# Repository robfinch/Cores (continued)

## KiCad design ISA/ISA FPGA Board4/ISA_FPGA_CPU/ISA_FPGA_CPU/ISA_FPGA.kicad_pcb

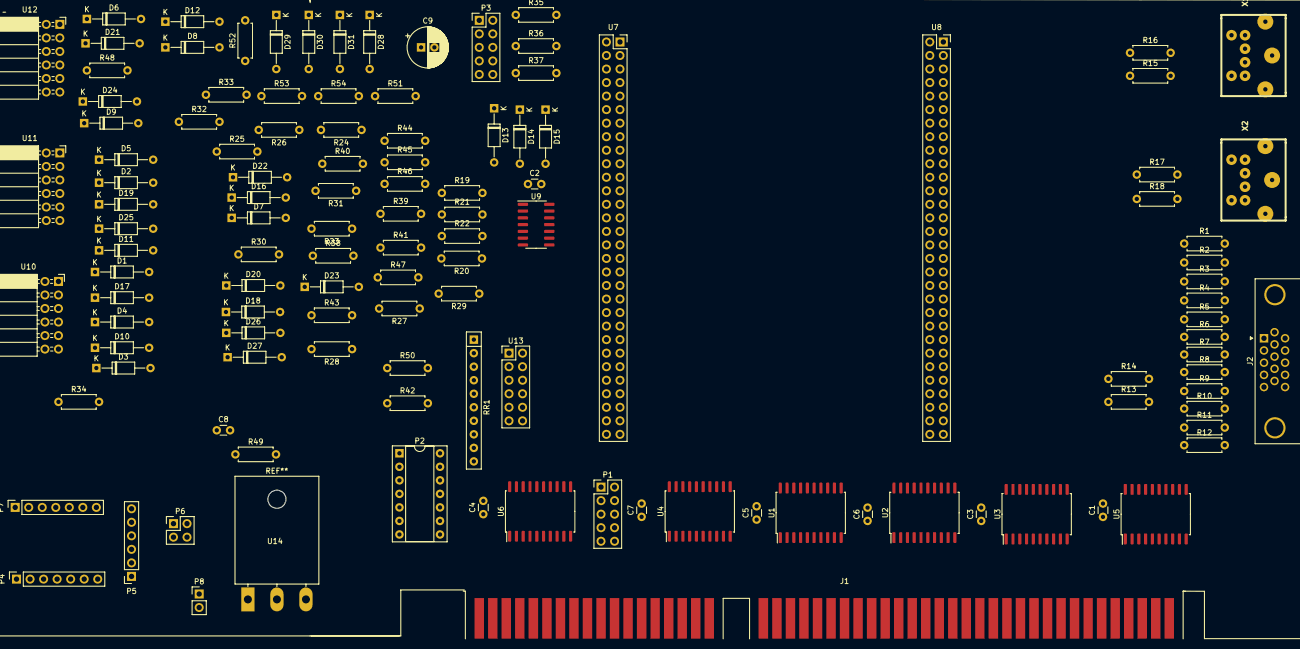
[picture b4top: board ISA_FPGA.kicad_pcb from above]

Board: 2 copper layers, 121 parts (0 on the bottom side), 207 nets, no tracks yet.

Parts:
C1, C2, C3, C4, C5, C6, C7, C8: 0.1; C_Disc_D3.0mm_W1.6mm_P2.50mm
C9: 10uF; CP_Radial_D7.5mm_P2.50mm
D1, D2, D3, D4, D5, D6, D7, D8, D9, D10, D11, D12, D13, D14, D15, D16, D17, D18, D19, D20, D21, D22, D23, D24, D25, D26, D27: ZPDxx; D_DO-35_SOD27_P10.16mm_Horizontal
D28, D29, D30, D31: LED; D_DO-35_SOD27_P10.16mm_Horizontal
J1: Bus_ISA_16bit; BUS_AT
J2: DE15; DSUB-15-HD_Female_Horizontal_P2.29x1.98mm_EdgePinOffset3.03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
P1, P3: CONN_5X2; PinHeader_2x05_P2.54mm_Vertical
P2: 14.31818MHz; DIP-14_W7.62mm_Socket
P4, P7: CONN_7; PinSocket_1x07_P2.54mm_Vertical
P5: CONN_6; PinSocket_1x06_P2.54mm_Vertical
P6: CONN_2X2; PinHeader_2x02_P2.54mm_Vertical
P8: CONN_2; PinHeader_1x02_P2.54mm_Vertical
R1, R5, R9: 510; R_Axial_DIN0207_L6.3mm_D2.5mm_P7.62mm_Horizontal
R2, R6, R10: 1k; R_Axial_DIN0207_L6.3mm_D2.5mm_P7.62mm_Horizontal
R3, R7, R11: 2k; R_Axial_DIN0207_L6.3mm_D2.5mm_P7.62mm_Horizontal
R4, R8, R12: 4k; R_Axial_DIN0207_L6.3mm_D2.5mm_P7.62mm_Horizontal
R13, R14, R35, R36, R37, R51, R52, R53, R54: 100; R_Axial_DIN0207_L6.3mm_D2.5mm_P7.62mm_Horizontal
R15, R16, R17, R18, R23, R24, R25, R26, R27, R28, R29, R30, R31, R32, R33, R34, R38, R39, R40, R41, R42, R43, R44, R45, R46, R47, R48, R49: 200; R_Axial_DIN0207_L6.3mm_D2.5mm_P7.62mm_Horizontal
R19, R20, R21, R22: 2k2; R_Axial_DIN0207_L6.3mm_D2.5mm_P7.62mm_Horizontal
R50: 10K; R_Axial_DIN0207_L6.3mm_D2.5mm_P7.62mm_Horizontal
RR1: 10k; R_Array_SIP10
U1, U2, U3, U4, U5, U6: 74LVC245; SOIC-20W_7.5x12.8mm_P1.27mm
U7, U8: CONN_30X2; PinSocket_2x30_P2.54mm_Vertical
U9: 74LVC06; SOIC-14_3.9x8.7mm_P1.27mm
U10, U11, U12: CONN_6x2; PinSocket_2x06_P2.54mm_Horizontal
U13: CONN_6x2; PinHeader_2x06_P2.54mm_Vertical
U14: LM3940; LMxx
X1, X2: MINI_DIN_6; PS2

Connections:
/A1: J1.61, U1.3
/A2: J1.60, U1.4
/A3: J1.59, U1.5
/A4: J1.58, U1.6
/A5: J1.57, U1.7
/A6: J1.56, U1.8
/A7: J1.55, U1.9
/A8: J1.54, U2.2
/A9: J1.53, U2.3
/A10: J1.52, U2.4
/A11: J1.51, U2.5
/A12: J1.50, U2.6
/A13: J1.49, U2.7
/A14: J1.48, U2.8
/A15: J1.47, U2.9
/A16: J1.46, U3.2
/A17: J1.45, U3.3
/A18: J1.44, U3.4
/A19: J1.43, U3.5
/A20: J1.88, U3.6
/A21: J1.87, U3.7
/A22: J1.86, U3.8
/A23: J1.85, U3.9
/A24: J1.84, U4.2
/A25: J1.83, U4.3
/A26: J1.82, U4.4
/ALE: J1.28, U4.5
/ANA0: R35.2, U8.11
/ANA1: R36.2, U7.26
/ANA2: R37.2, U7.25
/BLUE0: R4.1, U8.36
/BLUE1: R3.1, U8.34
/BLUE2: R2.1, U8.32
/BLUE3: R1.1, U8.30
/CFG0: RR1.2, U7.48, U13.1
/CFG1: RR1.3, U7.50, U13.3
/CFG2: RR1.4, U7.52, U13.5
/CFG3: RR1.5, U7.54, U13.7
/CFG4: RR1.6, U8.28, U13.9
/D0: J1.40, U5.2
/D1: J1.39, U5.3
/D2: J1.38, U5.4
/D3: J1.37, U5.5
/D4: J1.36, U5.6
/D5: J1.35, U5.7
/D6: J1.34, U5.8
/D7: J1.33, U5.9
/D8: J1.91, U6.9
/D9: J1.92, U6.8
/D10: J1.93, U6.7
/D11: J1.94, U6.6
/D12: J1.95, U6.5
/D13: J1.96, U6.4
/D14: J1.97, U6.3
/D15: J1.98, U6.2
/FA1: U1.17, U8.5
/FA2: U1.16, U8.7
/FA3: U1.15, U8.9
/FA4: U1.14, U8.10
/FA5: U1.13, U8.13
/FA6: U1.12, U8.15
/FA7: U1.11, U8.17
/FA8: U2.18, U8.19
/FA9: U2.17, U8.21
/FA10: U2.16, U8.23
/FA11: U2.15, U8.25
/FA12: U2.14, U8.27
/FA13: U2.13, U8.29
/FA14: U2.12, U8.31
/FA15: U2.11, U8.33
/FA16: U3.18, U8.49
/FA17: U3.17, U8.47
/FA18: U3.16, U8.45
/FA19: U3.15, U8.43
/FA20: U3.14, U8.41
/FA21: U3.13, U8.39
/FA22: U3.12, U8.37
/FA23: U3.11, U8.35
/FA24: U4.18, U8.51
/FA25: U4.17, U8.53
/FA26: U4.16, U8.55
/FALE: U4.15, U8.14
/FD0: U5.18, U7.20
/FD1: U5.17, U7.18
/FD2: U5.16, U7.16
/FD3: U5.15, U7.14
/FD4: U5.14, U7.12
/FD5: U5.13, U7.8
/FD6: U5.12, U7.6
/FD7: U5.11, U7.4
/FD8: U6.11, U7.38
/FD9: U6.12, U7.36
/FD10: U6.13, U7.34
/FD11: U6.14, U7.32
/FD12: U6.15, U7.30
/FD13: U6.16, U7.28
/FD14: U6.17, U7.24
/FD15: U6.18, U7.22
/FDBE*: U5.19, U6.19, U8.20
/FRX: R50.1, U8.26
/FTX: P6.3, U8.24
/FWR: R19.1, U5.1, U6.1, U8.16, U9.2
/GREEN0: R8.1, U8.44
/GREEN1: R7.1, U8.42
/GREEN2: R6.1, U8.40
/GREEN3: R5.1, U8.38
/HS: R13.1, U8.56
/IRQ: U8.22, U9.9
/IRQ*: P1.1, P1.3, P1.5, P1.7, P1.9, R21.1, U9.8
/KBDCLK: R15.1, U8.6
/KBDDAT: R16.1, U8.4
/LED0: R51.1, U7.40
/LED1: R52.1, U7.42
/LED2: R53.1, U7.44
/LED3: R54.1, U7.46
/MSECLK: R18.1, U8.12
/MSEDAT: R17.1, U8.8
/OSC: J1.30, R22.1, U9.4
/PMODA0: R23.1, U7.3
/PMODA1: R24.1, U7.5
/PMODA2: R25.1, U7.7
/PMODA3: R26.1, U7.9
/PMODA4: R38.2, U7.11
/PMODA5: R39.2, U7.13
/PMODA6: R40.2, U7.15
/PMODA7: R41.2, U7.17
/PMODB0: R31.1, U7.19
/PMODB1: R32.1, U7.21
/PMODB2: R33.1, U7.23
/PMODB3: R34.1, U7.27
/PMODB4: R46.2, U7.31
/PMODB5: R47.2, U7.33
/PMODB6: R48.2, U7.35
/PMODB7: R49.2, U7.37
/PMODC0: R27.1, U7.39
/PMODC1: R28.1, U7.41
/PMODC2: R29.1, U7.45
/PMODC3: R30.1, U7.49
/PMODC4: R42.2, U7.51
/PMODC5: R43.2, U7.53
/PMODC6: R44.2, U7.55
/PMODC7: R45.2, U7.56
/RDY: J1.41, R20.1, U9.6
/RDY*: U8.18, U9.5
/RED0: R12.1, U8.52
/RED1: R11.1, U8.50
/RED2: R10.1, U8.48
/RED3: R9.1, U8.46
/SEL0: J1.62, U1.2
/SEL1: J1.81, U4.6
/VCC33: C1.1, C2.1, C3.1, C4.1, C5.1, C6.1, C7.1, C9.1, R19.2, RR1.1, U1.1, U1.20, U2.1, U2.20, U3.1, U3.20, U4.1, U4.20, U5.20, U6.20, U10.11, U10.12, U11.11, U11.12, U12.11, U12.12, U14.VO, X1.5, X2.5
/VS: R14.1, U8.54
/WR*: J1.90, U9.1
GND: C1.2, C2.2, C3.2, C4.2, C5.2, C6.2, C7.2, C9.2, D1.2, D2.2, D3.2, D4.2, D5.2, D6.2, D7.2, D8.2, D9.2, D10.2, D11.2, D12.2, D13.2, D14.2, D15.2, D16.2, D17.2, D18.2, D19.2, D20.2, D21.2, D22.2, D23.2, D24.2, D25.2, D26.2, D27.2, D28.2, D29.2, D30.2, D31.2, J1.1, J1.10, J1.31, J1.80, J2.5, J2.6, J2.7, J2.8, J2.10, P2.4, P2.5, P2.6, P2.7, P3.1, P3.3, P3.5, P3.7, P3.9, P5.1, P7.7, U1.10, U1.19, U2.10, U2.19, U3.10, U3.19, U4.10, U4.19, U5.10, U6.10, U7.1, U7.2, U7.57, U7.58, U8.1, U8.2, U8.57, U8.58, U10.9, U10.10, U11.9, U11.10, U12.9, U12.10, U13.2, U13.4, U13.6, U13.8, U13.10, U13.12, U14.GND
unnamed: C8.1, P5.6
unnamed: D1.1, R30.2, U10.7
unnamed: D2.1, R26.2, U11.7
unnamed: D3.1, R34.2, U12.7
unnamed: D4.1, R29.2, U10.5
unnamed: D5.1, R25.2, U11.5
unnamed: D6.1, R33.2, U12.5
unnamed: D7.1, R28.2, U10.3
unnamed: D8.1, R24.2, U11.3
unnamed: D9.1, R32.2, U12.3
unnamed: D10.1, R27.2, U10.1
unnamed: D11.1, R23.2, U11.1
unnamed: D12.1, R31.2, U12.1
unnamed: D13.1, P3.10, R37.1
unnamed: D14.1, P3.6, R36.1
unnamed: D15.1, P3.2, R35.1
unnamed: D16.1, R40.1, U11.6
unnamed: D17.1, R45.1, U10.8
unnamed: D18.1, R49.1, U12.8
unnamed: D19.1, R41.1, U11.8
unnamed: D20.1, R44.1, U10.6
unnamed: D21.1, R48.1, U12.6
unnamed: D22.1, R39.1, U11.4
unnamed: D23.1, R43.1, U10.4
unnamed: D24.1, R47.1, U12.4
unnamed: D25.1, R38.1, U11.2
unnamed: D26.1, R42.1, U10.2
unnamed: D27.1, R46.1, U12.2
unnamed: D28.1, R51.2
unnamed: D29.1, R52.2
unnamed: D30.1, R53.2
unnamed: D31.1, R54.2
unnamed: J1.65, P1.2
unnamed: J1.66, P1.4
unnamed: J1.67, P1.6
unnamed: J1.68, P1.8
unnamed: J1.69, P1.10
unnamed: J2.1, R9.2, R10.2, R11.2, R12.2
unnamed: J2.2, R5.2, R6.2, R7.2, R8.2
unnamed: J2.3, R1.2, R2.2, R3.2, R4.2
unnamed: J2.13, R13.2
unnamed: J2.14, R14.2
unnamed: P2.8, P2.9, P2.10, P2.11, U9.3
unnamed: P5.3, P7.6, P8.2
unnamed: P5.4, P6.4
unnamed: P5.5, P6.2
unnamed: P6.1, R50.2
unnamed: R15.2, X1.6, X1.8
unnamed: R16.2, X1.1, X1.2
unnamed: R17.2, X2.1, X2.2
unnamed: R18.2, X2.6, X2.8
unnamed: X1.3, X2.3
VCC: J1.3, J1.29, J1.78, P2.14, P8.1, R20.2, R21.2, R22.2, U7.59, U7.60, U8.59, U8.60, U14.VI

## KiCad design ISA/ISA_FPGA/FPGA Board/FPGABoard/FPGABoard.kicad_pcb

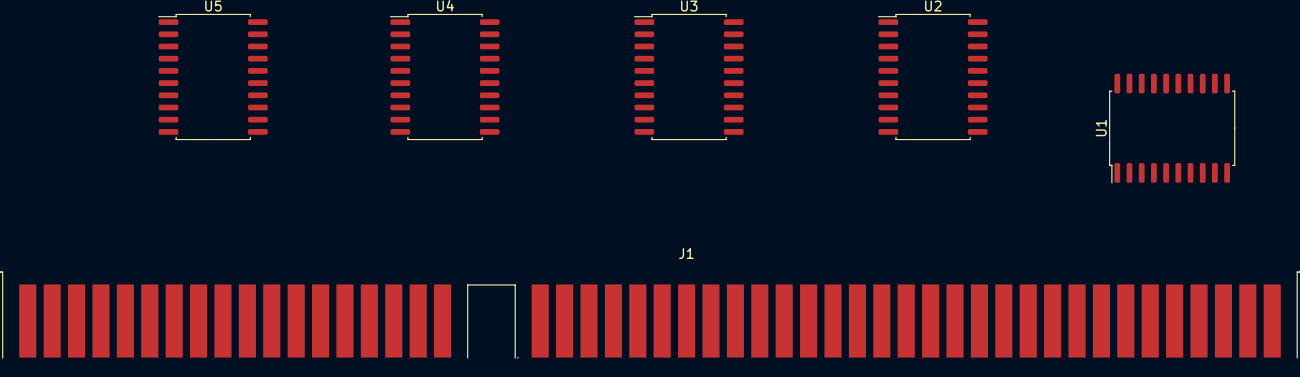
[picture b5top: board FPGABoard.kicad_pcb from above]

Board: 2 copper layers, 6 parts (0 on the bottom side), 8 nets, no tracks yet.

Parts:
J1: Bus_ISA_16bit; BUS_AT
U1, U2, U3, U4, U5: 74LVC245; SOIC-20W_7.5x12.8mm_P1.27mm

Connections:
/DB0: J1.40, U1.2
/DB1: J1.39, U1.3
/DB2: J1.38, U1.4
/DB3: J1.37, U1.5
/DB4: J1.36, U1.6
/DB5: J1.35, U1.7
/DB6: J1.34, U1.8
/DB7: J1.33, U1.9

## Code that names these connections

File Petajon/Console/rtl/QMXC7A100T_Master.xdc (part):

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set_property IOSTANDARD LVCMOS33 [get_ports {FAD[6]}]
set_property IOSTANDARD LVCMOS33 [get_ports {FAD[7]}]

set_property PACKAGE_PIN J25 [get_ports {FBEN}]

set_property IOSTANDARD LVCMOS33 [get_ports {FBEN}]
set_property IOSTANDARD LVCMOS33 [get_ports {FIRQ[0]}]
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set_property IOSTANDARD LVCMOS33 [get_ports {FIRQ[10]}]


set_property PACKAGE_PIN G4 [get_ports {FALE}]
set_property IOSTANDARD LVCMOS33 [get_ports {FALE}]
set_property PACKAGE_PIN F23 [get_ports {RDYN}]
set_property IOSTANDARD LVCMOS33 [get_ports {RDYN}]
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#set_property PACKAGE_PIN J4 [get_ports {ANA[1]}]
#set_property PACKAGE_PIN H4 [get_ports {ANA[2]}]

set_property PACKAGE_PIN E26 [get_ports {KBDDAT}]
set_property PACKAGE_PIN E25 [get_ports {KBDCLK}]
set_property IOSTANDARD LVCMOS33 [get_ports {KBDDAT}]
set_property IOSTANDARD LVCMOS33 [get_ports {KBDCLK}]
set_property PULLUP true [get_ports {KBDDAT}]
set_property PULLUP true [get_ports {KBDCLK}]

set_property PACKAGE_PIN H26 [get_ports {MSEDAT}]
set_property PACKAGE_PIN G22 [get_ports {MSECLK}]
set_property IOSTANDARD LVCMOS33 [get_ports {MSEDAT}]
set_property IOSTANDARD LVCMOS33 [get_ports {MSECLK}]
set_property PULLUP true [get_ports {MSEDAT}]
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set_property PACKAGE_PIN H9 [get_ports {randi}]
set_property IOSTANDARD LVCMOS33 [get_ports {randi}]

set_property PACKAGE_PIN A5 [get_ports {FDIOWN}]
set_property PACKAGE_PIN A4 [get_ports {FDIORN}]
set_property PACKAGE_PIN A2 [get_ports {FCS1FXN}]
set_property PACKAGE_PIN C2 [get_ports {FCS3FXN}]
set_property PACKAGE_PIN D4 [get_ports {INTRQ}]
set_property PACKAGE_PIN D5 [get_ports {DDIR}]
set_property PACKAGE_PIN B1 [get_ports {DBENN}]
set_property PACKAGE_PIN D1 [get_ports {RESETN}]
set_property PACKAGE_PIN G2 [get_ports {EN138}]
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set_property IOSTANDARD LVCMOS33 [get_ports {MS[2]}]

# HDMI
set_property -dict {PACKAGE_PIN AC26 IOSTANDARD TMDS_33} [get_ports HCLKN]
set_property -dict {PACKAGE_PIN AB26 IOSTANDARD TMDS_33} [get_ports HCLKP]
set_property -dict {PACKAGE_PIN Y26 IOSTANDARD TMDS_33} [get_ports {HD0N}]
set_property -dict {PACKAGE_PIN W25 IOSTANDARD TMDS_33} [get_ports {HD0P}]
set_property -dict {PACKAGE_PIN AA25 IOSTANDARD TMDS_33} [get_ports {HD1N}]
set_property -dict {PACKAGE_PIN Y25 IOSTANDARD TMDS_33} [get_ports {HD1P}]
set_property -dict {PACKAGE_PIN Y21 IOSTANDARD TMDS_33} [get_ports {HD2N}]
set_property -dict {PACKAGE_PIN W21 IOSTANDARD TMDS_33} [get_ports {HD2P}]

# Serial Bus Transmit
set_property -dict {PACKAGE_PIN L4 IOSTANDARD TMDS_33} [get_ports {FTCLKN}]
set_property -dict {PACKAGE_PIN M4 IOSTANDARD TMDS_33} [get_ports {FTCLKP}]
set_property -dict {PACKAGE_PIN K5 IOSTANDARD TMDS_33} [get_ports {FTDAT0N}]
set_property -dict {PACKAGE_PIN L5 IOSTANDARD TMDS_33} [get_ports {FTDAT0P}]
set_property -dict {PACKAGE_PIN J1 IOSTANDARD TMDS_33} [get_ports {FTDAT1N}]
set_property -dict {PACKAGE_PIN K1 IOSTANDARD TMDS_33} [get_ports {FTDAT1P}]
set_property -dict {PACKAGE_PIN M1 IOSTANDARD TMDS_33} [get_ports {FTDAT2N}]
set_property -dict {PACKAGE_PIN N1 IOSTANDARD TMDS_33} [get_ports {FTDAT2P}]
set_property IODELAY_GROUP iodelay0 [get_ports {FTCLKN, FTCLKP, FTDAT0N, FTDAT0P, FTDAT1N, FTDAT1P, FTDAT2N, FTDAT2P}]
set_property IODELAY_GROUP iodelay0 [get_cells uopcr1/TMDS_ClockingX/IDelayCtrlX]
set_property -dict {PACKAGE_PIN H1 IOSTANDARD TMDS_33} [get_ports {FTDAT3N}]
set_property -dict {PACKAGE_PIN H2 IOSTANDARD TMDS_33} [get_ports {FTDAT3P}]
set_property -dict {PACKAGE_PIN L2 IOSTANDARD TMDS_33} [get_ports {FTDAT4N}]
set_property -dict {PACKAGE_PIN M2 IOSTANDARD TMDS_33} [get_ports {FTDAT4P}]
set_property -dict {PACKAGE_PIN N2 IOSTANDARD TMDS_33} [get_ports {FTDAT5N}]
set_property -dict {PACKAGE_PIN N3 IOSTANDARD TMDS_33} [get_ports {FTDAT5P}]
set_property -dict {PACKAGE_PIN P3 IOSTANDARD TMDS_33} [get_ports {FTDAT6N}]
set_property -dict {PACKAGE_PIN R3 IOSTANDARD TMDS_33} [get_ports {FTDAT6P}]
set_property IODELAY_GROUP iodelay1 [get_ports {FTDAT3N, FTDAT3P, FTDAT4N, FTDAT4P, FTDAT5N, FTDAT5P, FTDAT6N, FTDAT6P}]
set_property IODELAY_GROUP iodelay1 [get_cells uopcr2/TMDS_ClockingX/IDelayCtrlX]
set_property -dict {PACKAGE_PIN P1 IOSTANDARD TMDS_33} [get_ports {FTDAT7N}]
set_property -dict {PACKAGE_PIN R1 IOSTANDARD TMDS_33} [get_ports {FTDAT7P}]
set_property -dict {PACKAGE_PIN T3 IOSTANDARD TMDS_33} [get_ports {FTDAT8N}]
set_property -dict {PACKAGE_PIN T4 IOSTANDARD TMDS_33} [get_ports {FTDAT8P}]
set_property -dict {PACKAGE_PIN R2 IOSTANDARD TMDS_33} [get_ports {FTDAT9N}]
set_property -dict {PACKAGE_PIN T2 IOSTANDARD TMDS_33} [get_ports {FTDAT9P}]
set_property -dict {PACKAGE_PIN U1 IOSTANDARD TMDS_33} [get_ports {FTDAT10N}]
set_property -dict {PACKAGE_PIN U2 IOSTANDARD TMDS_33} [get_ports {FTDAT10P}]
set_property IODELAY_GROUP iodelay2 [get_ports {FTDAT7N, FTDAT7P, FTDAT8N, FTDAT8P, FTDAT9N, FTDAT9P, FTDAT10N, FTDAT10P}]
set_property IODELAY_GROUP iodelay2 [get_cells uopcr3/TMDS_ClockingX/IDelayCtrlX]

# Serial Bus Receive
set_property -dict {PACKAGE_PIN T25 IOSTANDARD TMDS_33} [get_ports {FRCLKN}]
set_property -dict {PACKAGE_PIN T24 IOSTANDARD TMDS_33} [get_ports {FRCLKP}]
set_property -dict {PACKAGE_PIN P25 IOSTANDARD TMDS_33} [get_ports {FRDAT0N}]
set_property -dict {PACKAGE_PIN R25 IOSTANDARD TMDS_33} [get_ports {FRDAT0P}]
set_property -dict {PACKAGE_PIN N22 IOSTANDARD TMDS_33} [get_ports {FRDAT1N}]
set_property -dict {PACKAGE_PIN N21 IOSTANDARD TMDS_33} [get_ports {FRDAT1P}]
set_property -dict {PACKAGE_PIN P26 IOSTANDARD TMDS_33} [get_ports {FRDAT2N}]
set_property -dict {PACKAGE_PIN R26 IOSTANDARD TMDS_33} [get_ports {FRDAT2P}]
set_property -dict {PACKAGE_PIN K23 IOSTANDARD TMDS_33} [get_ports {FRDAT3N}]
set_property -dict {PACKAGE_PIN K22 IOSTANDARD TMDS_33} [get_ports {FRDAT3P}]
set_property -dict {PACKAGE_PIN J21 IOSTANDARD TMDS_33} [get_ports {FRDAT4N}]
set_property -dict {PACKAGE_PIN K21 IOSTANDARD TMDS_33} [get_ports {FRDAT4P}]
set_property -dict {PACKAGE_PIN H22 IOSTANDARD TMDS_33} [get_ports {FRDAT5N}]
set_property -dict {PACKAGE_PIN H21 IOSTANDARD TMDS_33} [get_ports {FRDAT5P}]
set_property -dict {PACKAGE_PIN G21 IOSTANDARD TMDS_33} [get_ports {FRDAT6N}]
set_property -dict {PACKAGE_PIN G20 IOSTANDARD TMDS_33} [get_ports {FRDAT6P}]
set_property -dict {PACKAGE_PIN K26 IOSTANDARD TMDS_33} [get_ports {FRDAT7N}]
set_property -dict {PACKAGE_PIN K25 IOSTANDARD TMDS_33} [get_ports {FRDAT7P}]
set_property -dict {PACKAGE_PIN M25 IOSTANDARD TMDS_33} [get_ports {FRDAT8N}]
set_property -dict {PACKAGE_PIN M24 IOSTANDARD TMDS_33} [get_ports {FRDAT8P}]
set_property -dict {PACKAGE_PIN L23 IOSTANDARD TMDS_33} [get_ports {FRDAT9N}]
set_property -dict {PACKAGE_PIN L22 IOSTANDARD TMDS_33} [get_ports {FRDAT9P}]
set_property -dict {PACKAGE_PIN N22 IOSTANDARD TMDS_33} [get_ports {FRDAT10N}]
set_property -dict {PACKAGE_PIN N21 IOSTANDARD TMDS_33} [get_ports {FRDAT10P}]
set_property PULLUP true [get_ports {FRCLKN}]
set_property PULLUP true [get_ports {FRCLKP}]
set_property PULLUP true [get_ports {FRDAT0N}]
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 
# VGA

set_property PACKAGE_PIN P6 [get_ports {AUD}]
set_property IOSTANDARD LVCMOS33 [get_ports {AUD}]

#set_property PACKAGE_PIN J26 [get_ports tg_compare_error]
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
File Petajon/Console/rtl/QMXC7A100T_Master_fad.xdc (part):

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set_property PACKAGE_PIN P23 [get_ports {FSEL[3]}]

set_property PACKAGE_PIN Y22 [get_ports {FRDYN}]
set_property PACKAGE_PIN P24 [get_ports {FBEN}]
set_property PACKAGE_PIN M6 [get_ports {FINT}]
set_property PACKAGE_PIN K25 [get_ports {FINTA}]
set_property IOSTANDARD LVCMOS33 [get_ports {FINTA}]
set_property IOSTANDARD LVCMOS33 [get_ports {FINT}]
set_property PULLUP true [get_ports {FINT}]
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set_property IOSTANDARD LVCMOS33 [get_ports {FAD[14]}]
set_property IOSTANDARD LVCMOS33 [get_ports {FAD[15]}]

set_property PACKAGE_PIN V23 [get_ports {FCDIR}]
set_property IOSTANDARD LVCMOS33 [get_ports {FCDIR}]
set_property PACKAGE_PIN K21 [get_ports {FBDIR}]
set_property IOSTANDARD LVCMOS33 [get_ports {FBDIR}]
set_property PACKAGE_PIN J25 [get_ports {FALE}]
set_property IOSTANDARD LVCMOS33 [get_ports {FALE}]
set_property PACKAGE_PIN G20 [get_ports {FRD}]
set_property IOSTANDARD LVCMOS33 [get_ports {FRD}]
set_property PACKAGE_PIN H21 [get_ports {RDYN}]
set_property IOSTANDARD LVCMOS33 [get_ports {RDYN}]
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#set_property PACKAGE_PIN J4 [get_ports {ANA[1]}]
#set_property PACKAGE_PIN H4 [get_ports {ANA[2]}]

set_property PACKAGE_PIN E26 [get_ports {KBDDAT}]
set_property PACKAGE_PIN E25 [get_ports {KBDCLK}]
set_property IOSTANDARD LVCMOS33 [get_ports {KBDDAT}]
set_property IOSTANDARD LVCMOS33 [get_ports {KBDCLK}]
set_property PULLUP true [get_ports {KBDDAT}]
set_property PULLUP true [get_ports {KBDCLK}]

set_property PACKAGE_PIN H26 [get_ports {MSEDAT}]
set_property PACKAGE_PIN G22 [get_ports {MSECLK}]
set_property IOSTANDARD LVCMOS33 [get_ports {MSEDAT}]
set_property IOSTANDARD LVCMOS33 [get_ports {MSECLK}]
set_property PULLUP true [get_ports {MSEDAT}]
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set_property PACKAGE_PIN N1 [get_ports {randi}]
set_property IOSTANDARD LVCMOS33 [get_ports {randi}]

set_property PACKAGE_PIN A5 [get_ports {FDIOWN}]
set_property PACKAGE_PIN A4 [get_ports {FDIORN}]
set_property PACKAGE_PIN A2 [get_ports {FCS1FXN}]
set_property PACKAGE_PIN C2 [get_ports {FCS3FXN}]
set_property PACKAGE_PIN D4 [get_ports {DRDYN}]
set_property PACKAGE_PIN D5 [get_ports {DDIR}]
set_property PACKAGE_PIN B1 [get_ports {DBENN}]
set_property PACKAGE_PIN D1 [get_ports {RESETN}]
set_property PULLUP true [get_ports {RESETN}]
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set_property IOSTANDARD LVCMOS33 [get_ports {MS[2]}]

# HDMI
set_property -dict {PACKAGE_PIN AC26 IOSTANDARD TMDS_33} [get_ports HCLKN]
set_property -dict {PACKAGE_PIN AB26 IOSTANDARD TMDS_33} [get_ports HCLKP]
set_property -dict {PACKAGE_PIN Y26 IOSTANDARD TMDS_33} [get_ports {HD0N}]
set_property -dict {PACKAGE_PIN W25 IOSTANDARD TMDS_33} [get_ports {HD0P}]
set_property -dict {PACKAGE_PIN AA25 IOSTANDARD TMDS_33} [get_ports {HD1N}]
set_property -dict {PACKAGE_PIN Y25 IOSTANDARD TMDS_33} [get_ports {HD1P}]
set_property -dict {PACKAGE_PIN Y21 IOSTANDARD TMDS_33} [get_ports {HD2N}]
set_property -dict {PACKAGE_PIN W21 IOSTANDARD TMDS_33} [get_ports {HD2P}]

# Serial Bus Transmit
set_property -dict {PACKAGE_PIN P1 } [get_ports FTCLK0N]
set_property -dict {PACKAGE_PIN R1 } [get_ports FTCLK0P]
set_property -dict {PACKAGE_PIN U1 } [get_ports {FTDAT0N}]
set_property -dict {PACKAGE_PIN U2 } [get_ports {FTDAT0P}]
set_property -dict {PACKAGE_PIN R2 } [get_ports {FTDAT1N}]
set_property -dict {PACKAGE_PIN T2 } [get_ports {FTDAT1P}]
set_property -dict {PACKAGE_PIN T3 } [get_ports {FTDAT2N}]
set_property -dict {PACKAGE_PIN T4 } [get_ports {FTDAT2P}]
 
# Serial Bus Receive
set_property -dict {PACKAGE_PIN T25 IOSTANDARD TMDS_33} [get_ports FRCLK0N]
set_property -dict {PACKAGE_PIN T24 IOSTANDARD TMDS_33} [get_ports FRCLK0P]
set_property -dict {PACKAGE_PIN P25 IOSTANDARD TMDS_33} [get_ports {FRDAT0N}]
set_property -dict {PACKAGE_PIN R25 IOSTANDARD TMDS_33} [get_ports {FRDAT0P}]
set_property -dict {PACKAGE_PIN M26 IOSTANDARD TMDS_33} [get_ports {FRDAT1N}]
set_property -dict {PACKAGE_PIN N26 IOSTANDARD TMDS_33} [get_ports {FRDAT1P}]
set_property -dict {PACKAGE_PIN P26 IOSTANDARD TMDS_33} [get_ports {FRDAT2N}]
set_property -dict {PACKAGE_PIN R26 IOSTANDARD TMDS_33} [get_ports {FRDAT2P}]
set_property PULLUP true [get_ports {FRCLK0N}]
set_property PULLUP true [get_ports {FRCLK0P}]
set_property PULLUP true [get_ports {FRDAT0N}]
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 
# VGA

set_property PACKAGE_PIN P6 [get_ports {AUD}]
set_property IOSTANDARD LVCMOS33 [get_ports {AUD}]

#set_property PACKAGE_PIN J26 [get_ports tg_compare_error]
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
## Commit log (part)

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2019-12-29 Gambit v5 - update
    - mem issue fix
    - branches in program counter
    - type refactoring
2019-12-29 Gambit v5 - doc update
2019-12-29 Gambit v5 - update
    - icache hit logic
    - decode flow controls
    - fetchn stage multiplex
2019-12-30 Gambit v5 - update
    - initial archive for compiler
2019-12-30 Gambit v5 - update
    - icache hit logic
2019-12-30 Gambit v5 - update
    - pipeline decode
    - multiply instruction
2020-01-01 Gambit v5 - update
2020-01-01 Gambit v5 - update
    - cr registers
2020-01-01 Gambit v5 -update
    - divider
2020-01-02 Gambit v5 SoC - archive
2020-01-03 Gambit v5 - update
    - sign/zero extend instr.
    - write buffer
    -
2020-01-03 Gambit v5 - update
    - mod instruction
    - remove prior valid
    - change state bits to bitset
    -
2020-01-05 Gambit v5 - update
    - additional pipelining
2020-01-05 Gambit v5 update
2020-01-06 Gambit v5 - update
    - timiing improvements
2020-01-07 rtf65004 - update
2020-01-07 Gambit v5 - update
    - micro-op engine
2020-01-09 Gambit v5 - update
    - floating-point unit
2020-01-09 Gambit v5 - update
    - docs
2020-01-09 Gambit v5 - update
    - issue block on same memory channel
2020-01-13 Gambit v5 - update
    - pmmu
2020-01-15 Gambit v5 - update
    - fp testing
2020-01-27 CS01 - update
2020-01-28 CS01 - update
    - boot rom,
    - basic rom
2020-01-28 CS01 - update
    - mmu
2020-01-28 CS01 - update
    - fmtk
2020-02-06 CS01 - update
    - change file extension
2020-02-10 Petajon - Initial archive
2020-02-13 Petajon - update
2020-02-14 CC64 - RISCV - update
2020-02-17 CC64 /AS64 - update
2020-02-20 CC64 - update
    - RISCV fix temporary reuse in GenIndex()
2020-03-03 Petajon - update memory
2020-03-05 S100_65816 - Initial archive
2020-03-06 ISA - FPGA Console Board - Initial Archive
2020-03-06 ISA - FPGA board
2020-03-08 ISA - update
    cad files for ISA video / cpu boards
2020-03-13 ISA Board4 - archive
2020-03-13 Petajon Console - update
2020-03-19 Gambit - update
2020-03-25 FT2020 - archive
2020-03-25 Thor2020 - initial archive
2020-03-25 FT2020 - update
2020-03-27 Thor2020 - update
2020-04-07 Gambit - update
    - add fetchbuffer
2020-04-11 Gambit - update
    - blocking vs non-blcoking assigns
2020-04-11 Thor2020 - posit arith
2020-04-14 Thor2020 - posit arithmetic
2020-04-16 Thor2020 - posit arithmetic
    added intToPosit
2020-04-16 Thor2020 - posit arithmetic update
2020-04-19 Thor2020 - posit arithmetic update
    add square root
2020-04-28 Thor2020 - posit arthmetic update
2020-05-10 hard-posit initial archive
2020-06-05 hardposit - update
2020-08-22 nvio - biu update
2020-08-26 asm68 - update
    - label as register list
2020-09-12 CS01 - update
    - remove $v0, $v1 references
2020-09-14 Proposals - update
2020-09-15 via6522 - update
    - add interrupt enable delay counter
2020-09-20 rtf64 - initial archive
2020-09-23 rtf64 - update
2020-09-24 Update rtf64.sv
    - add floating point
    - add key memory
    - add card memory
2020-09-24 RTF64 - update
    - floating point compares
    - card memory
2020-09-24 Update rtf64.sv
    - shift operations
2020-09-25 Update rtf64.sv
    - PMA checker
    - bitfield ops
2020-09-25 RTF64 - software update
2020-09-26 RTF64 - update
    - added trace feature
2020-09-27 Update rtf64.sv
    - 128,64,32 bus interface
    - L1 icache
    - JMPR / JSRR
2020-09-28 Update rtf64.sv
    - increase cache size
    - bytndx and wydndx immediate mode
    - cache command
2020-09-28 RTF64 - update
    - remove JMPR JSRR
    - add cn register
2020-09-29 RTF64 - update
    - fmtk port
    - JSL / RTL / JSR / RTS
2020-09-30 RTF64 - update
    - ctype
2020-10-02 RTF64 - update
    initial compiler archive
2020-10-06 RTF64 - v2 update
2020-10-07 RTF64 v2 - update
    - added compiler
    - added assembler
2020-10-08 RTF64 v2 - update
    - compiler refactorings
2020-10-09 RTF64 v2 - update
2020-10-10 RTF64 v2 - update
    - reformat stores
    - compiler refactorings
2020-10-12 RTF64 v2 - update
    - posit arithmetic
    - bit arrays
2020-10-14 RTF64 v2 - compiler update
    -
2020-10-15 RTF64 v2 - compiler update
2020-10-16 RTF64 v2 - RTL update
2020-10-16 RTF64 v2 - software update
    - compiler
    - assmbler
2020-10-17 RTF64 v2 - software update compiler
    - Int256 class
    - posit arithmetic
2020-10-20 RTF64 v2 - update
    - posit arithmetic
2020-10-20 RTF64 v2 - posit arithmetic RTL
2020-10-21 RTF64 v2 - compiler update
    - posits
    - array aggegates
2020-10-22 RTF64 v2 - cpu rtl code update
    - work on overlapped pipeline
2020-10-23 RTF64 v2 - cpu rtl code update
    - bypassing network
    -
2020-10-23 RTF64 v2 - cpu RTL update
    - posit arithmetic
    - next pc
2020-10-23 RTF64 v2 - cpu RTL update
2020-10-24 RTF64 v2 - update
    - xbus archive
2020-10-25 RTF64 v2 - xbus update
2020-10-26 RTF64 v2 - iupdate
    - xbus phase alignment, channel bond fifo
    - compiler default argument values
2020-10-27 RTF64 - compiler update
2020-10-30 RTF64 v2 - rtl code update
2020-10-31 RTF64 v2 - rtl code update
    - pipeline fixes in cpu
    -
2020-11-02 RTF64 v2 update
    - bitfield module
    - fp modules
    - posit
    - change to use packages
2020-11-05 RTF64 v2 - FPU update
2020-11-10 RTF64 v2 compiler update
    - updated FPP as well
    - support for variable argument lists
    - larger macro expansions
2020-11-11 RTF64 v2 - update
    - CC64 tests
2020-11-13 RTF64 v2 - cpu update
    - pipleine invalidation
2020-11-14 RTF64 v2 - update
    - move crres update back one cycle
2020-11-26 GlyphEdit - initial archive
2020-11-30 RTF64 v2 - software update
2020-12-04 nPower v1 - initial archive
2020-12-05 nPower V1 - update
2020-12-05 nPower v1 - update
    - added shift / rotate / multiply
2020-12-07 RTF64 v2 - update
    - register sets removal
2020-12-12 RTF64 - v2 - update
    - data cache
2020-12-13 nPower v1 update
2020-12-13 bin2ver - initial archive
    - utility to convert binary files to verilog statements
2020-12-13 Update nPower.sv
    - stall on sprs
2020-12-14 nPower v1 - rtl update
    - branch predictor
2020-12-17 RTF64 v2 - fpu update
    - decimal floating-point addsub
2020-12-19 RTF64 v2 - decimal floating-point
2020-12-20 RTF64 v2 - update decimal float
2020-12-21 nPower v1 update
2020-12-21 RTF64 v2 update
2020-12-23 nPower v1 - update
    - system call
2020-12-24 nPower v1 - update
    - examples
2021-01-19 RTF64 v2 - update
    - decimal floating-point
2021-06-29 Graphics Routines
    - an archive of old code
2021-06-29 Graphics - doc update
2021-07-11 Software - update
    - fpp preprocessor
2021-08-16 RISCV - IMAM proposal
2021-08-27 CS01 - update
    - zero transitions for IRQ in via6522
    - memory interface
2021-09-19 nPower - update
2021-09-25 nPower v1 - compiler
2021-09-29 rfPower v1 update
2021-10-14 Thor2021 - update
2021-10-16 Thor2021 update
2021-10-19 Thor move
2022-01-03 rf6809 - initial archive
2022-01-04 rf6809 - update
2022-01-15 rf6809 - update
    12-bit uart
2022-01-30 rf6809 - update
    - 6309 support
2022-01-31 Naa - initial archive
2022-02-02 rf6809 - updated docs
2022-02-04 rf6809 - update
    - bcd arith
2022-02-09 rf6809 - update
    - Femtiki
2022-02-12 rf6809 update
2022-02-12 rf6809 - update
    - OS components
2022-02-15 rf6809 - udpate
    - mpmc8
2022-02-16 rf6809 - update
    JTT
2022-02-18 rf6809 - update
    mpmc8
2022-02-21 rf6809 - update
    - decimal floating-point
2022-02-22 rf6809 - update
    - decimal float
2022-07-06 FAL6567 - update
2022-07-09 FAL6567 - update
    KiCad files
2022-07-13 FAL6567 - update
    - move old files from mainline
2022-07-29 RF65816SBC - archive
2022-07-29 RF65816 - update
2022-07-29 RF65816SBC - update
    Broken out Serial, SRAM, and VGA
2022-07-30 RF65816SBC - update
2022-08-02 ISA65816 - archive
2022-08-02 ISA65816 - update
2022-09-22 memory cores - mpmc10
    - initial archive
2022-09-26 Cores - update
    - moved video to its own repository
2022-09-26 Cores - update
    - moved memory folder to its own repository
2022-09-26 Glyph Edit - update
    - added support for .mem files
2022-09-26 GlyphEdit - update
2022-09-27 GlyphEdit - update
    - copy and paste char
2022-10-01 fasm - archive
2022-10-10 GlyphEdit - update
    - serialize bitmaps
2022-10-15 GlyphEdit - update
    - sprite animation
2022-10-23 lib - update
2022-11-01 rf68000 - archive
2022-11-02 rf68000 - update
2022-11-03 rf68000 - update
    - flag updates in IFETCH
2022-11-04 rf68000 - update
    - cpu test program
2022-11-07 rf68000 - update
    - cpu test
2022-11-12 rf68000 - update
    - assembler mods
2022-11-13 rf68000 - update
    - Tiny Basic
2022-11-14 rf68000 - moved to own repository
2022-11-21 rf65000 - update
2022-11-23 uart6551 - update
2022-11-27 Update uart6551.sv
    - zero output bus when not selected
2023-01-14 rf29xx - update
2023-02-28 Cores - update
    - new version of Datetime with config space and 32-bit bus
2023-03-05 Cores - update
2023-05-19 rfx32 - archive
2023-05-21 rfx32 - update
2023-06-12 Cores - update
    - fta bridges
    - PS2KBD and random
2023-06-12 rgb2dvi - update
2023-06-28 Cores - update
    - uart6551
2024-02-23 cores - update
    - bin2ver
2024-03-01 rf8088 - update
2024-03-13 - moved out to nPower repository
2024-03-18 - rf8088 - moved outwards
2024-03-20 rf6809 - move out to own repo
2024-08-08 Create uart6551_fta32.sv
    - MSI interrupt version
2024-08-18 fpp64 - update
    - added default macro arguments
    - modernized some of the string fn's
2024-08-18 fpp64 - update
    - make use of buffer struct
2024-08-19 fpp - update
    - adding assembler language support
2024-08-19 fpp64 - update
    - fix file includes
2024-08-19 fpp64 - update
    - adding repeat directive
2024-08-19 fpp64 - update
    - adding buffer position struct
    - updating internal docs
2024-08-20 fpp64 - update
    - iterative repeat statements
    - abort, incdir
2024-08-20 fpp64 - update
    - strip_quotes utility fn
    - rpt flag in GetMacroArg()
2024-08-20 fpp64 - update
    - buffer alloc flag
    - strip blank lines
2024-08-21 fpp64 - update
    - macro/repeat instance var
2024-08-21 fpp64 - update
    - refactor
    - rept code in separate file now
    consistent type names
2024-08-21 fpp64 - update
    - char to buf fn
    - backslash in char const stringize
2024-08-21 fpp64 - update
    - fixing the stringize operator (pasting broke)
2024-08-22 fpp64 - update
    - 64-bit expression parsing
    - suppress errors on unneeded values
2024-08-22 fpp64 - update
    - fix stringize issue
2024-08-22 fpp64 - update
    - increase supported number of args to 100
2024-08-26 fpp64 - update
    - major re-writing in progress
    - "collect" routines
    - recursive macro definitions
2024-08-26 fpp64 - update
    - reduce macro arguments
    - remove ETB marker from output
2024-08-26 fpp64 - update
    - tweak default macro arguments
2024-08-26 fpp64 - update
    - undef sym status in expr
    - fix elif op
    - macro arg subs
2024-08-27 fpp64 - update
    - refactor
    - split apart fpp.h
    - added header comments
2024-10-16 uart6551 - update
    - add sketch of connection to 6502
2024-10-16 uart6551 - update
    - connection to 6502
    - ddbb config block
2024-10-16 Update uart6551.sv
    - reset line on ack generator
2025-06-04 Cores - spi master update
    - converting to SystemVerilog
    - card detect and reset
2025-06-09 Cores - spi master update
2025-06-11 Update uart6551.sv
    - add big-endian interfacing
2025-06-20 Update uart6551.sv
    - add config block
2025-07-06 Cores - update
    - add ddbb wrappers for i2c and spi
2026-01-16 Cores - update
    - FPP 3.06
